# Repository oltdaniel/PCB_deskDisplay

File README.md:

# PCB Desk Display

The idea was to have a special purpose, small footprint PCB for connecting an I²C Display, Button and Status LED.

## The PCB

The PCB including the ESP32-C3 Antenna has a total footprint of `20mmx30mm`. The files can be found in [`./pcb`](./pcb).

## The Code

The code currently is only a small placeholder to test the different parts of the PCB. The files can be found in [`./code`](./code) in form of a PlatformIO project.

## License

Enjoy the work and do what you want. `CERN OHL v2 Permissive`

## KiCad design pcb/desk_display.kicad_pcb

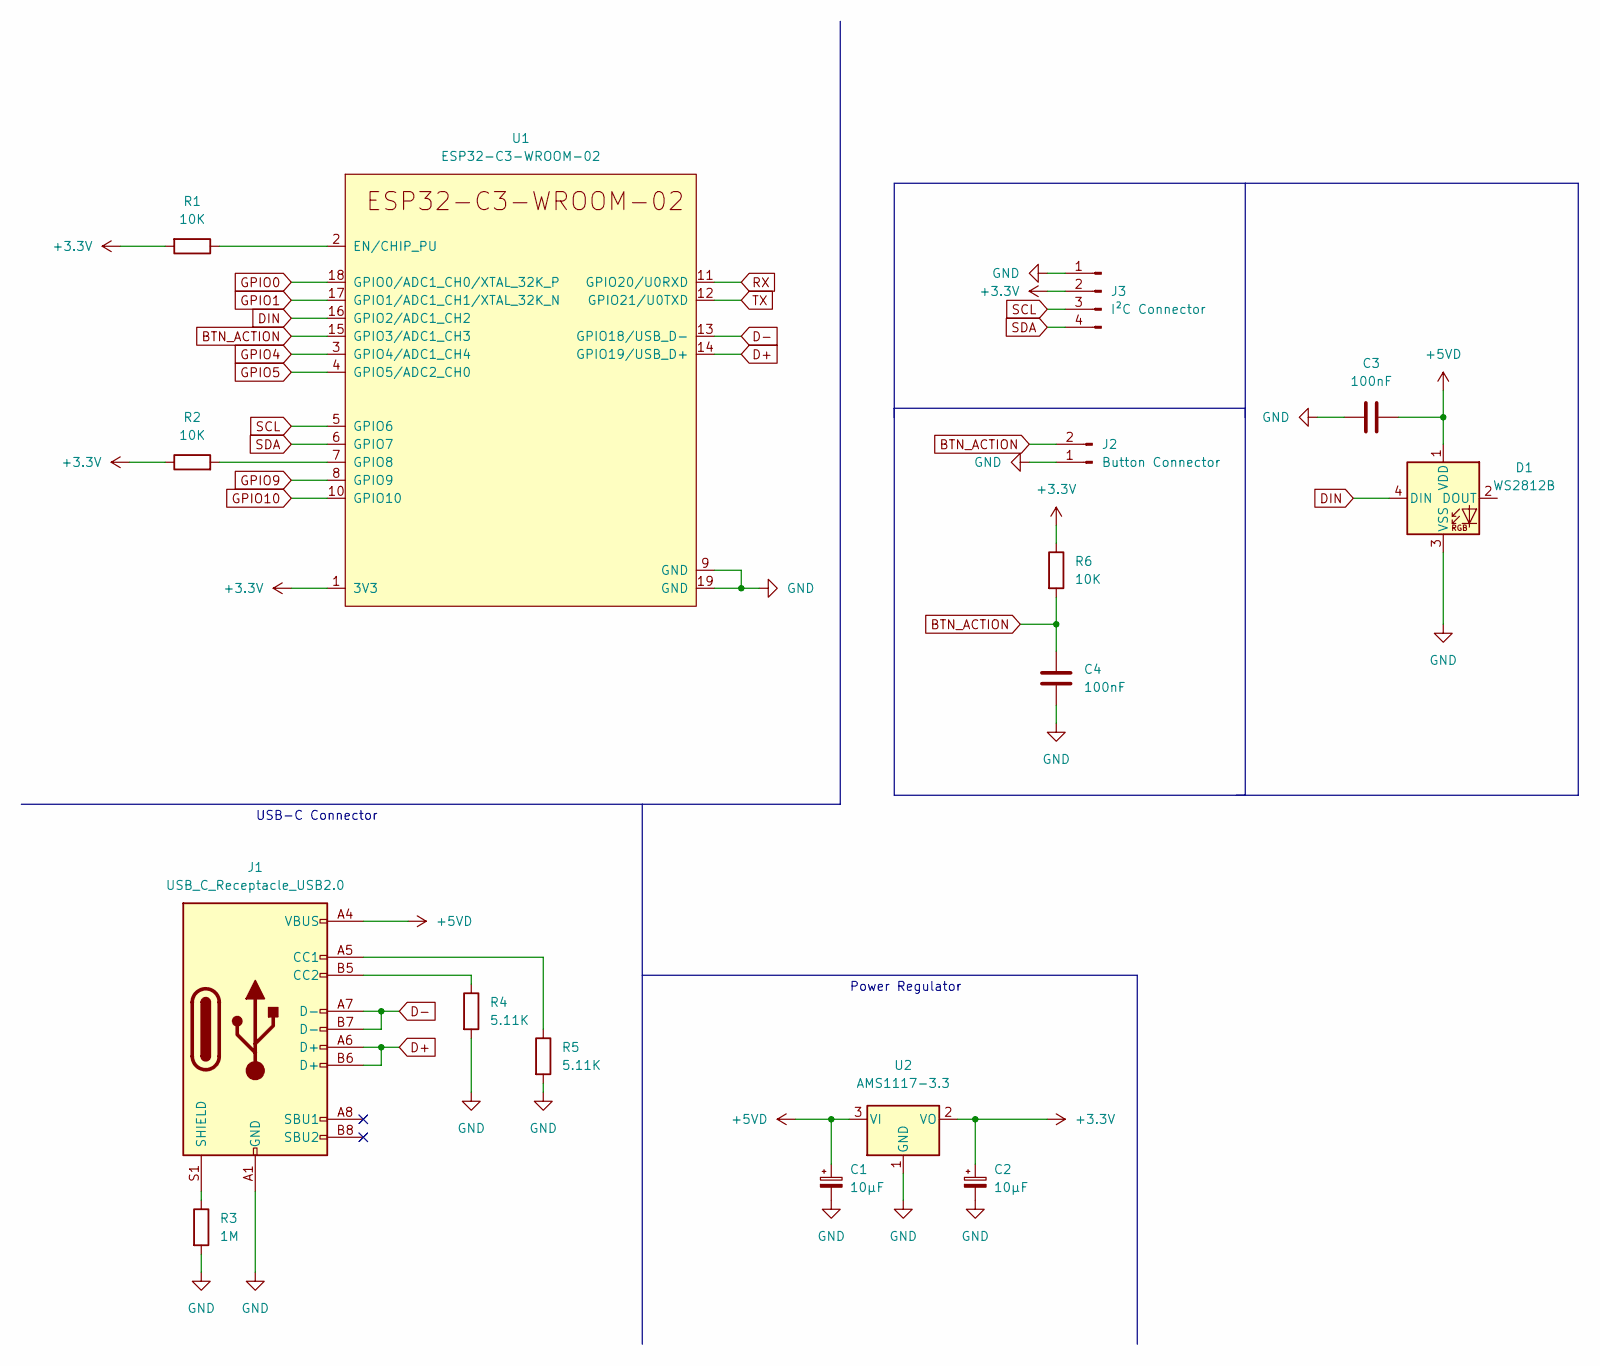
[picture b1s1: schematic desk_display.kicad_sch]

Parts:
C1, C2: 10µF; C_0603_1608Metric
C3, C4: 100nF; C_0603_1608Metric
D1: WS2812B; LED_WS2812B_PLCC4_5.0x5.0mm_P3.2mm
J1: USB_C_Receptacle_USB2.0; USB_C_Receptacle_Palconn_UTC16-G
J2: Button Connector; PinHeader_1x02_P2.00mm_Vertical
J3: I²C Connector; PinHeader_1x04_P2.00mm_Vertical
R1, R2, R6: 10K; R_0603_1608Metric
R3: 1M; R_0603_1608Metric
R4, R5: 5.11K; R_0603_1608Metric
U1: ESP32-C3-WROOM-02
U2: AMS1117-3.3; SOT-223-3_TabPin2

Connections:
+3.3V: C2.1, J3.2, R1.2, R2.1, R6.1, U1.1 (3V3), U2.2 (VO)
+5VD: C1.1, C3.1, D1.1 (VDD), J1.A4 (VBUS), J1.A9 (VBUS), J1.B4 (VBUS), J1.B9 (VBUS), U2.3 (VI)
BTN_ACTION: C4.1, J2.2, R6.2, U1.15 (GPIO3/ADC1_CH3)
D+: J1.A6 (D+), J1.B6 (D+), U1.14 (GPIO19/USB_D+)
D-: J1.A7 (D-), J1.B7 (D-), U1.13 (GPIO18/USB_D-)
DIN: D1.4 (DIN), U1.16 (GPIO2/ADC1_CH2)
GND: C1.2, C2.2, C3.2, C4.2, D1.3 (VSS), J1.A1 (GND), J1.A12 (GND), J1.B1 (GND), J1.B12 (GND), J2.1, J3.1, R3.2, R4.2, R5.2, U1.9 (GND), U1.19 (GND), U2.1 (GND)
GPIO0: U1.18 (GPIO0/ADC1_CH0/XTAL_32K_P)
GPIO1: U1.17 (GPIO1/ADC1_CH1/XTAL_32K_N)
GPIO4: U1.3 (GPIO4/ADC1_CH4)
GPIO5: U1.4 (GPIO5/ADC2_CH0)
GPIO9: U1.8 (GPIO9)
GPIO10: U1.10 (GPIO10)
unnamed: J1.A5 (CC1), R5.1
unnamed: J1.B5 (CC2), R4.1
unnamed: J1.S1 (SHIELD), R3.1
unnamed: R1.1, U1.2 (EN/CHIP_PU)
unnamed: R2.2, U1.7 (GPIO8)
RX: U1.11 (GPIO20/U0RXD)
SCL: J3.3, U1.5 (GPIO6)
SDA: J3.4, U1.6 (GPIO7)
TX: U1.12 (GPIO21/U0TXD)

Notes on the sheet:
USB-C Connector
Power Regulator

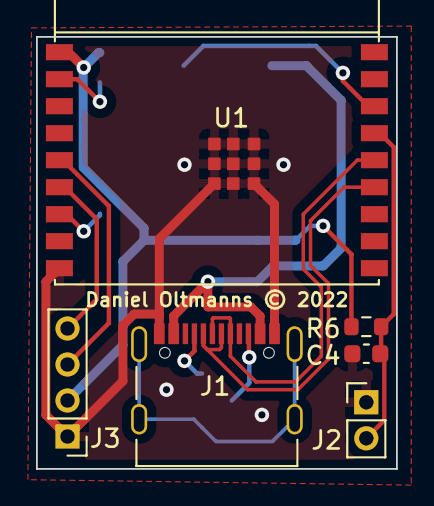
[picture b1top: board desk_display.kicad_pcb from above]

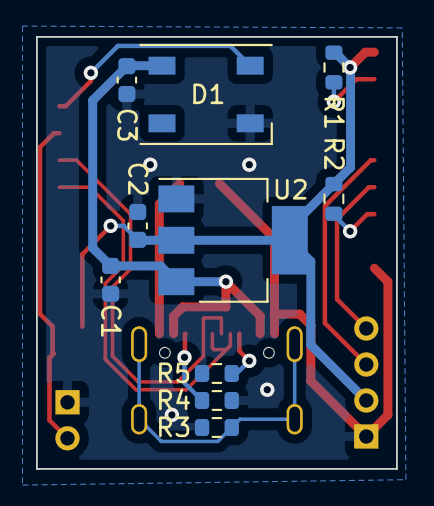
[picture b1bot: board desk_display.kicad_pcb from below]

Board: 2 copper layers, 20.0 x 24.0 mm, 16 parts (10 on the bottom side), 14 nets.

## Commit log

2022-07-17 kicad gitignore
2022-07-17 removed debug code + updated step file

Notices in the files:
pcb/desk_display.kicad_pcb:
Daniel Oltmanns © 2022
